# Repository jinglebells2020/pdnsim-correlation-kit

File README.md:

# pdnsim DC correlation kit, revision C — frozen predictions

This repository publishes the **frozen, blind predictions** of the pdnsim DC correlation kit
(revision C) **before any board has been measured**. pdnsim is Simulibrium's DC IR-drop
(voltage-drop) analysis for KiCad boards.

A prediction is blind only if it was published before the measurement. These files make it
possible to check, later, that the measured results were compared with predictions fixed in
advance.

**Measured accuracy: none yet.** Nothing here is a measurement. The numbers in each
`manifest.json` are pdnsim's nominal predictions for the drawn copper of each ordered board
variant, at the fab's published nominal materials.

## What is here

| Path | What it is |
|---|---|
| `kit/correlation/DC-A@JLCPCB/` | DC-A test board, as ordered from JLCPCB: KiCad board, footprints, fab files, structure list, `manifest.json` (the frozen predictions) |
| `kit/correlation/DC-A@OSHPark/` | DC-A test board, as ordered from OSH Park |
| `kit/correlation/DC-B@JLCPCB/` | DC-B 4-layer test board, as ordered from JLCPCB |
| `kit/correlation/README.md` | The kit's own description (structures, variants, the freeze procedure) |
| `SHA256SUMS` | SHA-256 of every file under `kit/` |
| `LICENSE` | Creative Commons Attribution 4.0 International |

Each variant folder holds the same set of files:

| File | What it is |
|---|---|
| `manifest.json` | The frozen predictions (schema `pdnsim-kit-manifest/2.0.0`) |
| `STRUCTURES.md` | Human-readable list of the test structures and their pads |
| `*.kicad_pcb`, `*.kicad_pro`, `fp-lib-table`, `kit.pretty/` | KiCad board, project and footprint library |
| `fab/` | Gerbers, drill files, job file and `FAB_NOTES.txt`, as sent to the fab |

Every file under `kit/` is a **byte-for-byte copy** of the same path at commit
`6089f18215fb33b6517cfd34e1e2b68f254b26f4` of the project's private development repository,
the commit that froze the three ordered variants. The kit's README refers to project files that
are not in this repository; they are not needed to check the predictions.

## Freeze record

- Frozen at: **2026-09-30T22:37:21Z** (the `frozen_at` field of each manifest).
- Freeze tag named in each manifest: `kit-revC-frozen-20260930`.
- Manifest schema: `pdnsim-kit-manifest/2.0.0`, status `frozen`.

| Variant | SHA-256 of `manifest.json` |
|---|---|
| `DC-A@JLCPCB` | `0380305942eb3074b9b0c43881a4c84dd80b9ef34d34a300505127b344b5820a` |
| `DC-A@OSHPark` | `88b3b00db004893e5cdd9a4e5d3682f16e9d32318634c68260069ee0fdbd8033` |
| `DC-B@JLCPCB` | `d98b1a52961c6c96555394d8a66fdd6cf5af46fae24080acda33ddb1f5f6e8e6` |

## Verifying the files

From the repository root:

```sh
sha256sum -c SHA256SUMS          # Linux
shasum -a 256 -c SHA256SUMS      # macOS
```

Every line must report `OK`. The same check runs in CI on every push
(`.github/workflows/verify-checksums.yml`), and `.gitattributes` stops git from rewriting line
endings, so a fresh clone matches the frozen bytes on any platform.

The boards open in KiCad 9 (board file format `20241229`). Opening a board in KiCad can
create local files (`*.kicad_prl`, backups); they are ignored by `.gitignore` and are not part
of the kit.

Not included: the fourth, provisional variant (DC-A2@JLCPCB, not ordered) and the order records
(order numbers and prices).

## Licence

The files in this repository are licensed under the Creative Commons Attribution 4.0
International licence (CC BY 4.0); see `LICENSE`.

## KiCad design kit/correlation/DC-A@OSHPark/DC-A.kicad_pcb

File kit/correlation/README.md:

# pdnsim DC correlation kit (ROADMAP M13), revision C

Manufacturable DC test boards ("coupons") for measuring how well pdnsim predicts real copper.
Every structure is a single net with on-board Kelvin (4-wire) force and sense pads, so the
quantity measured on the bench is exactly the one pdnsim computes:

    R4 = [V(S+) − V(S−)] / I

where S+ and S− are sense pads that carry no current and I is forced between F+ and F−.

> **Nothing in this folder is a measurement.** The expected values in each `manifest.json`
> are pdnsim's own nominal predictions for the drawn copper at the ordered variant's published
> nominal copper and plating, at 20 °C. No board has been fabricated or measured. pdnsim has
> **no measured accuracy** until boards are measured and the data processed; nothing in this
> kit may be quoted as one.
>
> **Status: the three ordered variants are FROZEN; DC-A2@JLCPCB is PROVISIONAL.** The
> manifests of DC-A@JLCPCB, DC-B@JLCPCB and DC-A@OSHPark were frozen at
> 2026-09-30T22:37:21Z from the committed (ordered) boards, before any board arrived or was
> measured (`freeze_tag` `kit-revC-frozen-20260930`, pdnsim commit `8ec4955508c0`, clean
> tree); DC-A2@JLCPCB was not ordered and stays provisional. The predictions use each
> structure's own via model — the corrected model (`copper.via_model: corrected`, DECISIONS
> D70–D72) for every structure, the lumped barrel for the Kelvin vias, whose quiet-side taps
> exclude the land spreading (D173). Do not compare a measurement with a provisional
> manifest.

Revision C replaces revision B (K2S/K2V/K4, 100 × 127–155 mm, never fabricated). It follows
the market research's test-board plan: three coupon designs of ≤ 100 × 100 mm, 18 boards from
two fabs (DECISIONS D150–D176 record every change and every dropped item, D400 the pre-order
re-check; the plan and its review are in `docs/kit-revC/`).

## Designs and ordered variants

A **design** is one artwork; an **ordered variant** is a design at one fab with that fab's
published nominal materials. Each variant has its own folder, board file, fab files and
manifest; the variants of one design share the artwork byte for byte (checked at build: every
Gerber except the job file, and the drill files).

| Variant (folder) | Design | Fab, quantity | Outer copper (nominal) | Plating (nominal) | Finish | Mask | Serial |
|---|---|---|---|---|---|---|---|
| `DC-A@JLCPCB/` | DC-A, 2 layers | JLCPCB, 5 | 1 oz, 35 µm | 18 µm | ENIG | green | JLCPCB `A1-0001…` |
| `DC-A@OSHPark/` | DC-A, 2 layers | OSH Park, 3 | 1 oz, 35.56 µm (1.4 mil) | 25.4 µm (1 mil) | ENIG | purple | hand-written |
| `DC-A2@JLCPCB/` | DC-A (same Gerbers) | JLCPCB, 5 | **2 oz**, 70 µm | 18 µm | ENIG | **blue** | JLCPCB `A2-0001…` |
| `DC-B@JLCPCB/` | DC-B, 4 layers | JLCPCB, 5 | 1 oz / inner 0.5 oz (15.2 µm) | 18 µm | ENIG | green | JLCPCB `B-0001…` |

Both designs are **99.06 × 99.06 mm** (39 steps of the 2.54 mm probe grid; JLCPCB's ≤ 100 ×
100 mm price tier), 1.6 mm FR-4, four 3.2 mm unplated mounting holes 4 mm from the corners.
DC-B is JLCPCB's **JLC04161H-7628** stackup (Cu 35 µm / 7628 prepreg 0.2104 mm / Cu 15.2 µm /
core 1.065 mm / Cu 15.2 µm / 7628 prepreg 0.2104 mm / Cu 35 µm, published; identical to its
default 1.6 mm 4-layer build). JLCPCB publishes no 2-layer core thickness: the DC-A core is an
**assumption** (1.51 mm at 1 oz, 1.44 mm at 2 oz) measured by micrometer on the thickness
islands and on the microsection. Every nominal carries its source (the fab page and the date
it was fetched) in the manifest's `variant.sources`; assumptions are listed in
`variant.assumptions`.

DC-A and DC-A2 are the same artwork ordered in two copper weights: they are told apart by the
**mask colour** (green / blue, an order-form option that leaves the Gerbers identical), the
JLCPCB serial prefix, and the silkscreen tick boxes `CU 1OZ □ 2OZ □  FAB JLC □ OSH □` (tick the
board's variant on arrival; a 2 oz board is also about 14 % heavier). Record the variant of
every board in the measurement file.

### What is on the boards

**DC-A** (2 layers; probed from **both faces**: front-only structures sit over back-only
ones, and back structures have their pads on B.Cu and are probed with the board flipped — the
pad grid is symmetric, so one pogo plate serves both faces):

* both faces — plane pairs with 1, 4 and 8 vias (VA1, VA4, VA8); single Kelvin vias at 0.3
  and 0.5 mm drill (KV-030, KV-050); 20-via daisy chains at both drills (DC-030W, DC-050W); a
  stacked F/B cross pair (VDP-F3/VDP-B3); via witnesses (WIT-V) and facing F/B copper
  islands for the board thickness (TK1–TK3);
* front — a 1 mm × 88 mm bar with taps 78.74 mm apart (LB-F-100, a millivolt-level check),
  the neck to 1/5 width (NK1), the 90° corner (LC), 0.5/1/2 mm bridges along x and a 0.5 mm
  bridge along y (BR-F-…), F.Cu crosses (VDP-F1, VDP-F2);
* back — a 38 × 38 mm pour with a 5 × 5 grid of keyhole sense taps fed at the midpoints of
  two edges through 4 mm feeds with 2 × 2 mm force pads (PM, the plane map; its force wires
  are **soldered**), a slotted strip (SL1-B), a 5 mm bar (BR-B-500X), a 0.5 mm bridge
  (BR-B-050X), B.Cu crosses (VDP-B1, B2, B4), and a serpentine copper RTD with a 2.8 × 5 mm
  thermocouple pad (RTD, role *thermometer*).

**DC-B** (4 layers; every pad on the front): a PDN with a BGA-like copper load on
In2 (supply) / In1 (return) planes, a 0.3 mm supply connector F → In2 and a 0.5 mm return
connector In1 → B with a B.Cu bus, and taps on all four layers (configurations P1–P7: the
pour → vias → inner plane → back path); a 26 × 16 mm In1 plane split by a 1 mm gap and joined
by a 2 mm bridge, fed through 4 mm wide, 5 mm long feeds (SP); the neck on In1 (NK1-I1); crosses on all four layers (VDP-F1, VDP-B1,
VDP-I1-1/2, VDP-I2-1/2); 0.5 and 2 mm inner bridges (BR-I1-…, BR-I2-…); the 0.25 mm strap
bridge on F.Cu (BR-F-025X); full-span Kelvin vias at both drills (KV-FB, KV-FB-050); WIT-V
and TK1–TK3.

Each variant's `STRUCTURES.md` lists every structure and configuration with pads, nominal
R4, convergence, suggested current, expected sense voltage, self-heating estimate and the
triplets the noise rule needs.

### What the research asked for and did not get (details in DECISIONS)

The 50 mm pour is 38 mm (same 5 × 5 taps; tap voltages of a scaled sheet are scale-invariant);
VA2, the 1 mm and 2 mm y-bridges, LC-I1, a DC-B RTD and a separate layer-path structure were
dropped for space (the PDN carries the layer path); the via arrays are 1, 4 and 8 vias, not 1,
4, 9 and 16 (16 barrels in parallel are about 0.1 mΩ, below the plane spreading that already
dominates VA8); the "JLCJLCJLCJLC" order-number marker is
not on the boards because **JLCPCB no longer prints order numbers** (since May 2026, and asks
customers not to add the string): the boards carry a 2 × 10 mm solid silkscreen square in the
top margin for JLCPCB's free serial number instead.

## Folder contents

| File | What |
|---|---|
| `ORDERING.md` | every order-form field per variant, the OSH Park upload, prices, what to archive |
| `ORDERED.json` | per variant: upload zip, board and artwork SHA-256 (written by `pdnsim kit --zip`); the order block is filled in by hand when ordering |
| `<variant>/<design>.kicad_pcb` | the board (KiCad 9). Zone fills are KiCad's own (refilled with KiCad's zone filler at build time), so the fab, KiCad's DRC and pdnsim see the same copper. The variants of one design differ only in the stackup section |
| `<variant>/<design>.kicad_pro` | the design rules the board was checked against |
| `<variant>/fp-lib-table`, `kit.pretty/` | the kit's footprints |
| `<variant>/fab/` | Gerbers (all copper layers, masks, silkscreens, outline), the Gerber job file (the variant's copper and finish), Excellon drill files (PTH and NPTH separate), creation-date lines removed so they are reproducible, and `FAB_NOTES.txt` (what the boards must be, for that fab) |
| `<variant>/manifest.json` | schema `pdnsim-kit-manifest/2.0.0`: the variant and its cited nominals, status (provisional / frozen), provenance (pdnsim version, git commit, clean-tree flag, via model), every structure, pad (with its layer), 4-wire configuration, nominal prediction, suggested currents with the self-heating estimate, and the design checks |
| `<variant>/STRUCTURES.md` | a readable table generated from `manifest.json` |

## Provisional → frozen (before any measurement)

A blind prediction is blind only if it was published before the measurement. The order
(on 2026-09-30, steps 1–3 were done for DC-A@JLCPCB, DC-B@JLCPCB and DC-A@OSHPark — frozen
at 2026-09-30T22:37:21Z, tag `kit-revC-frozen-20260930` created locally; publishing the tag,
step 4, is the founder's decision; DC-A2@JLCPCB is not ordered and stays at step 1):

1. **Before ordering:** the manifests are `status: provisional`. Order the boards from the
   committed fab files (`ORDERING.md`); `pdnsim kit kit/correlation --zip DIR` writes the upload zips and
   records their hashes and the board hashes in `ORDERED.json`; fill in the order block (order
   number, date, price, serial range, the stackup screenshot) and commit it.
2. **The via-model correction is merged** (DECISIONS D70–D72; the merge: D173). Every
   structure predicts with its own model (`structures[].via_model`; `nominal_model.via_model`
   is `corrected`): the Kelvin vias `lumped`, every other structure `corrected`. The manifests
   were regenerated from the committed boards (`pdnsim kit kit/correlation --from-boards`);
   the boards and fab files did not change.
3. **Freeze** on a clean checkout: `pdnsim kit kit/correlation --freeze`. It refuses (exit 2)
   while the via-model correction is missing, while the source tree has uncommitted changes, or
   when a board differs from the one recorded in `ORDERED.json`; otherwise it re-predicts from
   the committed boards (the boards and fab files are not touched and must still be the
   generator's output) and writes `status: frozen`, `frozen_at` (UTC) and `freeze_tag`.
4. **Publish before the first reading:** commit, create the tag named in `freeze_tag`, push it
   to the public remote (a third party then attests its time) and record the tag and the
   release URL in the measurement file (`kits[].release`). `pdnsim correlate` refuses a
   provisional manifest unless `--allow-provisional` and states in every measured result
   whether it is blind (docs/CORRELATION.md §8).

## Ordering (summary; every field is in `ORDERING.md`)

* **JLCPCB** (DC-A, DC-A2, DC-B; one combined shipment): upload `DC-A_JLCPCB_revC.zip`,
  `DC-A2_JLCPCB_revC.zip`, `DC-B_JLCPCB_revC.zip` (the variant id with `_` for `@`: JLCPCB's
  uploader refuses `@` in a file name; D400); FR-4,
  1.6 mm, **ENIG** (a surcharge; **not OSP**, which JLCPCB's form excludes from physical contact
  areas — every pad here is spring-probed; **never HASL** — solder in an open via barrel
  changes its resistance by tens of per cent), vias **tented** (DC-A, DC-A2) or **plugged**
  (DC-B: JLCPCB's 4-layer form has no Tented; a via JLCPCB cannot ink-plug is to be tented;
  never open, never epoxy- or copper-filled), outer
  copper 1 oz (DC-A, DC-B) or **2 oz** (DC-A2), DC-B stackup **JLC04161H-7628** with inner
  copper 0.5 oz, mask green (DC-A, DC-B) or **blue** (DC-A2), Mark on PCB → serial number only
  at the specified position (prefixes `A1-`, `A2-`, `B-`), *Confirm Production File*, and the
  PCB Remark from `ORDERING.md` (JLCPCB reads no text inside the zip; each variant's is also in
  its `FAB_NOTES.txt`; DC-B has its own: plugged vias, the drills to plug, no fill).
* **OSH Park** (DC-A, 3 boards): upload `DC-A_OSHPark_revC.zip` (or the board file
  `DC-A_OSHPark.kicad_pcb`), 2 Layer
  Prototype service (1 oz, ENIG, purple); $5 per square inch per set of three, free shipping.
* Order all three JLCPCB designs **and** the OSH Park set: the fab-to-fab and 1 oz / 2 oz
  comparisons need them all. Keep one board of each variant for a microsection after its
  readings.

## Design rules (rev C)

One rule set valid for JLCPCB 2-layer 1 oz and 2 oz, JLCPCB 4-layer and OSH Park 2-layer, with
margin; the sources are quoted in `pdnsim.kit.rules.RULE_SOURCES` (pages fetched 2026-09-27)
and every value is in each manifest's `rules`:

* track ≥ 0.25 mm (the sense spokes, RTD lines and the 0.25 mm bridge are at it; JLCPCB 2 oz
  minimum 0.16 mm with ±20 % width tolerance; OSH Park 6 mil); clearance ≥ 0.25 mm; **same-net
  gaps ≥ 0.25 mm** (JLCPCB's same-net spacing; checked by the kit's topology check, which KiCad
  cannot do);
* vias follow JLCPCB's via rule (diameter ≥ hole + 0.1 mm, 0.15 mm preferred; "vias are treated
  differently from pads"): DC-A 0.30/0.75 and 0.50/1.00 mm, DC-B 0.30/0.70 and 0.50/0.90 mm;
  every trace-fed land/drill ≤ 2.5 (the via-model correction's validated domain, checked at
  build); **every plated hole is a via**, witnesses included, so the drill files have one
  plated tool per drill; the drill file's sizes are **finished** holes (the fabs' convention),
  while pdnsim's barrel (either via model) reads them as the drilled diameter — each
  manifest's variant assumptions give the resulting bias of prediction (a) per drill (D172);
  no surcharge on JLCPCB's form for a via hole ≥ 0.3 mm and a diameter ≥ 0.4 mm;
* hole-to-hole ≥ 0.45 mm, hole to other copper ≥ 0.30 mm, copper to edge ≥ 0.5 mm, structures
  ≥ 3 mm from the edge, no copper within 1 mm of a mounting hole, no mask opening within 4 mm
  of a mounting-hole centre (washer);
* solder mask 1:1 on the pads; every via land ≥ 0.20 mm from any mask opening (JLCPCB's 2 oz
  mask bridge; checked at build); every via covered by mask in the Gerbers (tented; JLCPCB
  plugs DC-B's 4-layer vias, D400);
* silkscreen text ≥ 1.0 mm high with a ≥ 0.16 mm stroke, ≥ 0.15 mm from every pad (JLCPCB's
  pad-to-silkscreen rule, in the DRC rules); a silkscreen ID next to every structure and a role
  label next to every pad;
* no thermal reliefs anywhere in a structure (zones connect pads solid); a netless balancing
  pour at a 0.5 mm gap on every layer.

`kicad-cli pcb drc` with the board's own project rules reports **0 violations and 0
unconnected items** on every variant (recorded in each `manifest.json`).

## How the structures are built

* **Probe pads** are single SMD pads (1.6 mm sense pads; force pads as wide as the conductor,
  except the plane map's 2 × 2 mm pads), every pad centre on the **2.54 mm grid** from the
  board's top-left corner (front view). Back pads are on B.Cu; the board width is a whole
  number of grid steps, so they are on the grid of the flipped board too. Inner and
  opposite-layer structures are reached through vias: force vias outside the sense span,
  zero-current sense vias for sense.
* **Force feeds** reach from a force pad (or force-via row) to the nearest tap over ≥ 2 × the
  conductor width. The manifest's **injection check** solves each structure with a 0.25 mm
  probe tip anywhere on each force pad and with ±10 % scatter between the barrels of each
  force-via group: every reading must change by ≤ 0.02 %.
* **Sense taps** are dead-end 0.25 mm spokes from the conductor edge, or keyholes (an island
  joined by one spoke) where a sense point sits inside a plane; the plane map's spokes run
  across the current, so a tap reads its hole centre whatever the hole's etch.
* **No pad lies in a current path**: the DC-B BGA load is copper only (balls, dogbones and
  straps are drawn as copper, not pads). The manifest's **topology check** proves on the
  finished board that each net has exactly its intended copper pieces, via lands and pads,
  that every pad is a dead end, and that same-net gaps are ≥ 0.25 mm — between pieces and
  inside one piece (a slot or a pinch; D176).
* **van der Pauw crosses** (1 mm arms) on every measured layer, spread over the board; the
  manifest records pdnsim's finite-contact error of each drawn cross (must be ≤ 0.1 %) and
  `STRUCTURES.md` lists the two crosses nearest each validation structure.
* **Witnesses:** WIT-V holds two vias of each drill, in the same Excellon tool as the measured
  vias, for the microsection (barrel wall, finished hole, land registration); TK1–TK3 are
  facing 3 × 3 mm bare-copper islands on F.Cu and B.Cu for a micrometer reading of the board
  thickness (the barrel length of every via prediction).

## Currents and self-heating

Each structure's `current` gives I_max and the three levels I_max, I_max/√2, I_max/2 (the
zero-power fit removes steady heating). I_max is the largest current within the structure's
cap (1 A; the plane map 3 A; the RTD 20 mA) whose **heuristic** self-heating estimate of the
sensed copper stays within 0.5 °C (RTD 0.02 °C): a whole-board thin-fin model (FR-4 plus the
board's copper, still air at 20 W/m²K from both faces, no credit for probes, leads or a
backing plate) fed by pdnsim's own loss map at 1 A plus the force contacts, **plus a local
line-source term** for every element: the rise of a conductor above the copper around it
through the FR-4 (the pour across its gap, the nearest copper above and below), which the fin
alone misses and which dominates on the narrow bridges and bars (review MET-1, D171). The
estimate is conservative in named respects (no conduction along a conductor to its wide ends,
no credit for the fixture) but it is not a bound. The plan assumes spring probes of **≤ 20 mΩ**
per force contact (the plane map: soldered leads); the manifest gives the extra rise per 10 mΩ
of contact (`delta_t_per_10mohm_contact_c`) and the current allowed with soldered force leads
(`i_max_soldered_a`). Record the two-wire force-path resistance of every reading
(`two_wire_ohm`): `pdnsim correlate` estimates the contacts from it and reports the extra
heating they imply (`FORCE_CONTACT`, a warning above the limit). `triplets_per_level` is the
number of current-reversal triplets per level for a zero-power reading with the structure's
`noise_target_rel` (0.1 %; the crosses 0.3 %, their spatial copper spread being several %) at
0.3 µV reading noise; `STRUCTURES.md` and the manifest's `summary` give the bench time.

## Measuring (summary; the protocol is [docs/CORRELATION.md](../../docs/CORRELATION.md))

* Support the board on a full-area insulating plate with reliefs for the other face's pads,
  joints and the thermocouple; probe the front first, then solder the plane-map force wires
  and probe the back.
* Current reversal (+I, −I, +I) at each level, levels in ascending order or after the board
  has returned to equilibrium; log the temperature (the RTD tracks drift to ~0.02 K once
  calibrated against the thermocouple pad).
* van der Pauw: all four configurations of each cross; the general vdP equation.
* Micrometer every board's thickness on TK1–TK3 with a contact ≤ 2.5 mm centred on each island
  (a flat anvil sits on the mask around it; docs/CORRELATION.md §3, D400); after the readings,
  section one board per variant through WIT-V (and chain barrels): wall thickness and finished
  hole per drill.
* Record the readings in a measurement file (`pdnsim correlate --template
  kit/correlation/DC-A@JLCPCB/manifest.json --serial A1-0001 --output meas.yaml`) and run
  `pdnsim correlate meas.yaml --out DIR`. `pdnsim correlate --self-test` checks that pipeline
  on synthetic data — it is not a measurement.

## Regenerating

```bash
pdnsim kit --list                                  # designs, variants, status
pdnsim kit kit/correlation                         # every variant; needs KiCad 9 (pcbnew + kicad-cli)
pdnsim kit kit/correlation -c DC-A --copper 2oz    # one variant (DC-A2@JLCPCB)
pdnsim kit kit/correlation --zip OUT               # + upload zips (no '@'), OSH Park board, SHA256SUMS
pdnsim kit kit/correlation --from-boards           # re-predict from the committed boards
pdnsim kit /tmp/k --no-kicad --no-predictions      # quick pdnsim-only build (no fab files)
```

The build is deterministic: the same pdnsim and KiCad versions give byte-identical boards, fab
files and zips (the manifests also record the pdnsim commit they were built from).
`tests/unit/test_correlation_boards.py` checks the committed files against the generator and
re-computes predictions; `tests/unit/test_kit_variants.py` the variants, freeze rules and
zips; `tests/e2e/test_correlation_boards_kicad.py` (KiCad) re-runs the refill, DRC and fab
export.

## Known limitations

* The DC-A core thickness and the finished copper of every variant are nominal values until
  measured (micrometer, vdP crosses, microsection); JLCPCB publishes no finished 2 oz thickness
  and the DC-A2 plating is assumed equal to the 1 oz plating (use DC-A2's own microsection).
* The predictions are PROVISIONAL until frozen. The via structures use the corrected via model
  (the Kelvin vias the lumped barrel), which agrees with a 3-D reference, not with a
  measurement; each structure's `notes` list what the via model leaves out (D71).
* Etch bias is measured by the bridges (F.Cu along x and y, B.Cu along x on DC-A, F.Cu and
  the inner layers along x on DC-B) and applied by `pdnsim correlate` to prediction (b) to
  first order; a direction without a bridge borrows the other with a bound, DC-B's B.Cu is only
  bounded.
* The 0.5 mm vias are at JLCPCB's tenting limit; a leaky tent on OSH Park's ENIG boards may
  put nickel into a barrel (inspect every tent over a measured via; the microsection shows it).
* ENIG covers every mask-free pad: the micrometer reading over TK1–TK3 (contact ≤ 2.5 mm on
  the island) includes the finish of both faces (+6–12 µm, ≤ 0.8 % of the span; not
  subtracted); a flat anvil would add the mask and silkscreen around the islands (+10–80 µm)
  and is not a valid reading.
* Prediction (a) reads each drawn via drill as the drilled diameter; if the fab finishes the
  hole as drawn, the real barrels have 7–16 % less resistance than (a) (per drill and variant
  in the manifest's assumptions); (b) uses the microsection and is immune.
* The self-heating estimate is a heuristic (conservative in named respects, not a bound), not
  a thermal prediction; the three-level fit measures the real heating.

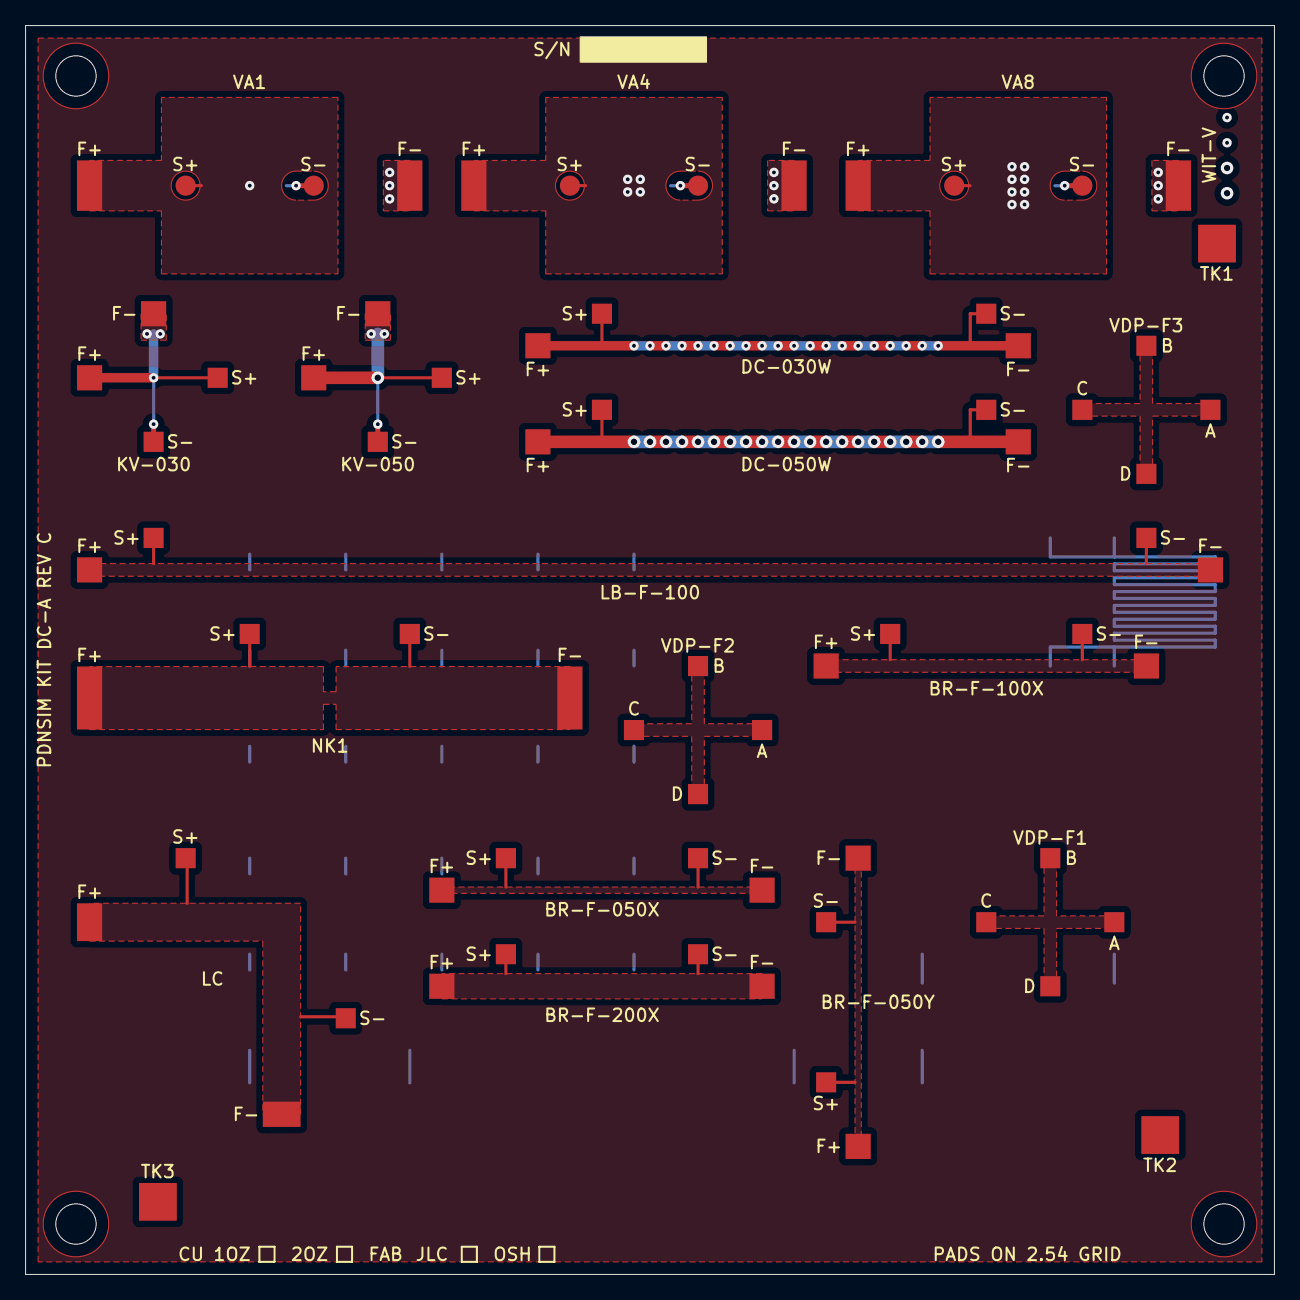
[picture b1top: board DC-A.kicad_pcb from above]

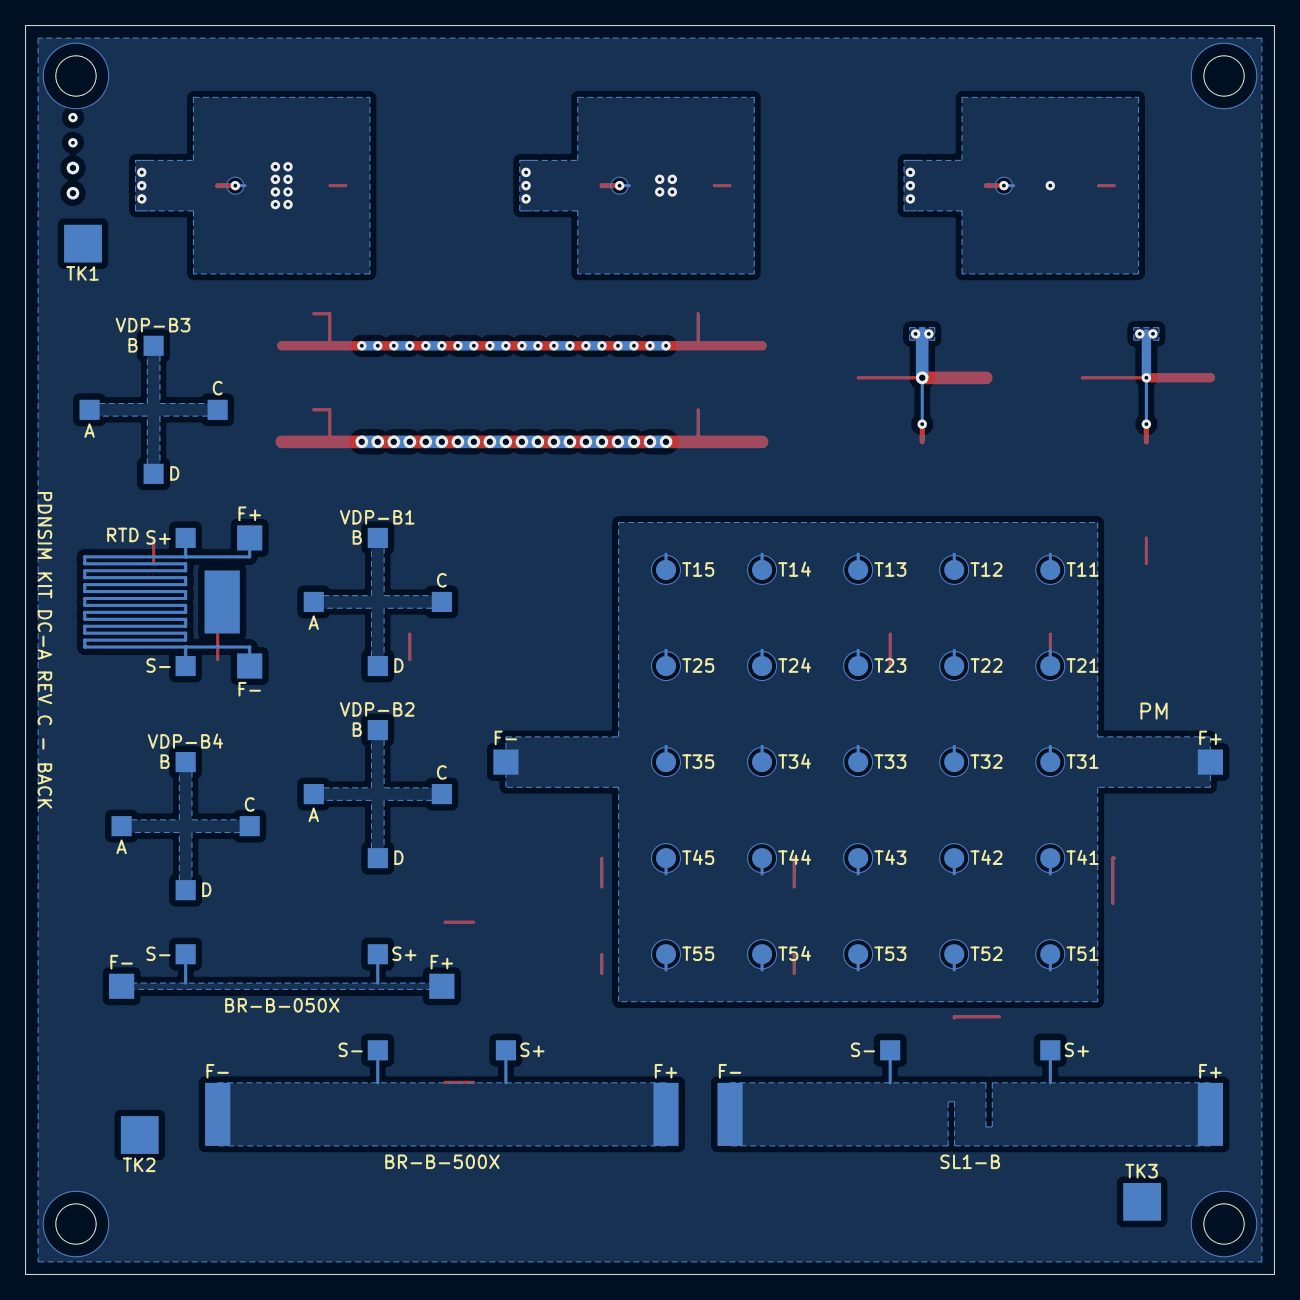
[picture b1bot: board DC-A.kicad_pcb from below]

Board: 2 copper layers, 99.1 x 99.1 mm, 138 parts (63 on the bottom side), 26 nets.

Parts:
BRB050X_FM, BRB050X_FP: ForcePad_2.0x2.0mm
BRB050X_SM, BRB050X_SP, BRB500X_SM, BRB500X_SP: ProbePad_1.6x1.6mm
BRB500X_FM, BRB500X_FP: ForcePad_2.0x5.0mm
BRF050X_FM, BRF050X_FP, BRF050Y_FM, BRF050Y_FP, BRF100X_FM, BRF100X_FP, BRF200X_FM, BRF200X_FP: ForcePad_2.0x2.0mm
BRF050X_SM, BRF050X_SP, BRF050Y_SM, BRF050Y_SP, BRF100X_SM, BRF100X_SP, BRF200X_SM, BRF200X_SP: ProbePad_1.6x1.6mm
DC030W_FM, DC030W_FP, DC050W_FM, DC050W_FP: ForcePad_2.0x2.0mm
DC030W_SM, DC030W_SP, DC050W_SM, DC050W_SP: ProbePad_1.6x1.6mm
H1, H2, H3, H4: MountingHole_3.2mm
KV030_FM, KV030_FP, KV050_FM, KV050_FP: ForcePad_2.0x2.0mm
KV030_SM, KV030_SP, KV050_SM, KV050_SP: ProbePad_1.6x1.6mm
LBF100_FM, LBF100_FP: ForcePad_2.0x2.0mm
LBF100_SM, LBF100_SP: ProbePad_1.6x1.6mm
LC_FM: ForcePad_3.0x2.0mm
LC_FP: ForcePad_2.0x3.0mm
LC_SM: ProbePad_1.6x1.6mm
LC_SP: ProbePad_1.6x1.6mm
NK1_FM, NK1_FP: ForcePad_2.0x5.0mm
NK1_SM, NK1_SP: ProbePad_1.6x1.6mm
PM_FM: ForcePad_2.0x2.0mm
PM_FP: ForcePad_2.0x2.0mm
PM_T11, PM_T12, PM_T13, PM_T14, PM_T15, PM_T21, PM_T22, PM_T23, PM_T24, PM_T25, PM_T31, PM_T32, PM_T33, PM_T34, PM_T35, PM_T41, PM_T42, PM_T43, PM_T44, PM_T45, PM_T51, PM_T52, PM_T53, PM_T54, PM_T55: ProbePad_D1.6mm
RTD_FM: ForcePad_2.0x2.0mm
RTD_FP: ForcePad_2.0x2.0mm
RTD_SM: ProbePad_1.6x1.6mm
RTD_SP: ProbePad_1.6x1.6mm
RTD_W1: ThermocouplePad_2.8x5.0mm
SL1B_FM, SL1B_FP: ForcePad_2.0x5.0mm
SL1B_SM, SL1B_SP: ProbePad_1.6x1.6mm
TK1_W1, TK1_W2, TK2_W1, TK2_W2, TK3_W1, TK3_W2: ThicknessIsland_3.0x3.0mm
VA1_FM, VA1_FP, VA4_FM, VA4_FP, VA8_FM, VA8_FP: ForcePad_2.0x4.0mm
VA1_SM, VA1_SP, VA4_SM, VA4_SP, VA8_SM, VA8_SP: ProbePad_D1.6mm
VDPB1_A, VDPB1_B, VDPB1_C, VDPB1_D, VDPB2_A, VDPB2_B, VDPB2_C, VDPB2_D, VDPB3_A, VDPB3_B, VDPB3_C, VDPB3_D, VDPB4_A, VDPB4_B, VDPB4_C, VDPB4_D: ProbePad_1.6x1.6mm
VDPF1_A, VDPF1_B, VDPF1_C, VDPF1_D, VDPF2_A, VDPF2_B, VDPF2_C, VDPF2_D, VDPF3_A, VDPF3_B, VDPF3_C, VDPF3_D: ProbePad_1.6x1.6mm

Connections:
BR-B-050X: BRB050X_FM.1, BRB050X_FP.1, BRB050X_SM.1, BRB050X_SP.1
BR-B-500X: BRB500X_FM.1, BRB500X_FP.1, BRB500X_SM.1, BRB500X_SP.1
BR-F-050X: BRF050X_FM.1, BRF050X_FP.1, BRF050X_SM.1, BRF050X_SP.1
BR-F-050Y: BRF050Y_FM.1, BRF050Y_FP.1, BRF050Y_SM.1, BRF050Y_SP.1
BR-F-100X: BRF100X_FM.1, BRF100X_FP.1, BRF100X_SM.1, BRF100X_SP.1
BR-F-200X: BRF200X_FM.1, BRF200X_FP.1, BRF200X_SM.1, BRF200X_SP.1
DC-030W: DC030W_FM.1, DC030W_FP.1, DC030W_SM.1, DC030W_SP.1
DC-050W: DC050W_FM.1, DC050W_FP.1, DC050W_SM.1, DC050W_SP.1
KV-030: KV030_FM.1, KV030_FP.1, KV030_SM.1, KV030_SP.1
KV-050: KV050_FM.1, KV050_FP.1, KV050_SM.1, KV050_SP.1
LB-F-100: LBF100_FM.1, LBF100_FP.1, LBF100_SM.1, LBF100_SP.1
LC: LC_FM.1, LC_FP.1, LC_SM.1, LC_SP.1
NK1: NK1_FM.1, NK1_FP.1, NK1_SM.1, NK1_SP.1
PM: PM_FM.1, PM_FP.1, PM_T11.1, PM_T12.1, PM_T13.1, PM_T14.1, PM_T15.1, PM_T21.1, PM_T22.1, PM_T23.1, PM_T24.1, PM_T25.1, PM_T31.1, PM_T32.1, PM_T33.1, PM_T34.1, PM_T35.1, PM_T41.1, PM_T42.1, PM_T43.1, PM_T44.1, PM_T45.1, PM_T51.1, PM_T52.1, PM_T53.1, PM_T54.1, PM_T55.1
RTD: RTD_FM.1, RTD_FP.1, RTD_SM.1, RTD_SP.1
SL1-B: SL1B_FM.1, SL1B_FP.1, SL1B_SM.1, SL1B_SP.1
VA1: VA1_FM.1, VA1_FP.1, VA1_SM.1, VA1_SP.1
VA4: VA4_FM.1, VA4_FP.1, VA4_SM.1, VA4_SP.1
VA8: VA8_FM.1, VA8_FP.1, VA8_SM.1, VA8_SP.1
VDP-B1: VDPB1_A.1, VDPB1_B.1, VDPB1_C.1, VDPB1_D.1
VDP-B2: VDPB2_A.1, VDPB2_B.1, VDPB2_C.1, VDPB2_D.1
VDP-B3: VDPB3_A.1, VDPB3_B.1, VDPB3_C.1, VDPB3_D.1
VDP-B4: VDPB4_A.1, VDPB4_B.1, VDPB4_C.1, VDPB4_D.1
VDP-F1: VDPF1_A.1, VDPF1_B.1, VDPF1_C.1, VDPF1_D.1
VDP-F2: VDPF2_A.1, VDPF2_B.1, VDPF2_C.1, VDPF2_D.1
VDP-F3: VDPF3_A.1, VDPF3_B.1, VDPF3_C.1, VDPF3_D.1

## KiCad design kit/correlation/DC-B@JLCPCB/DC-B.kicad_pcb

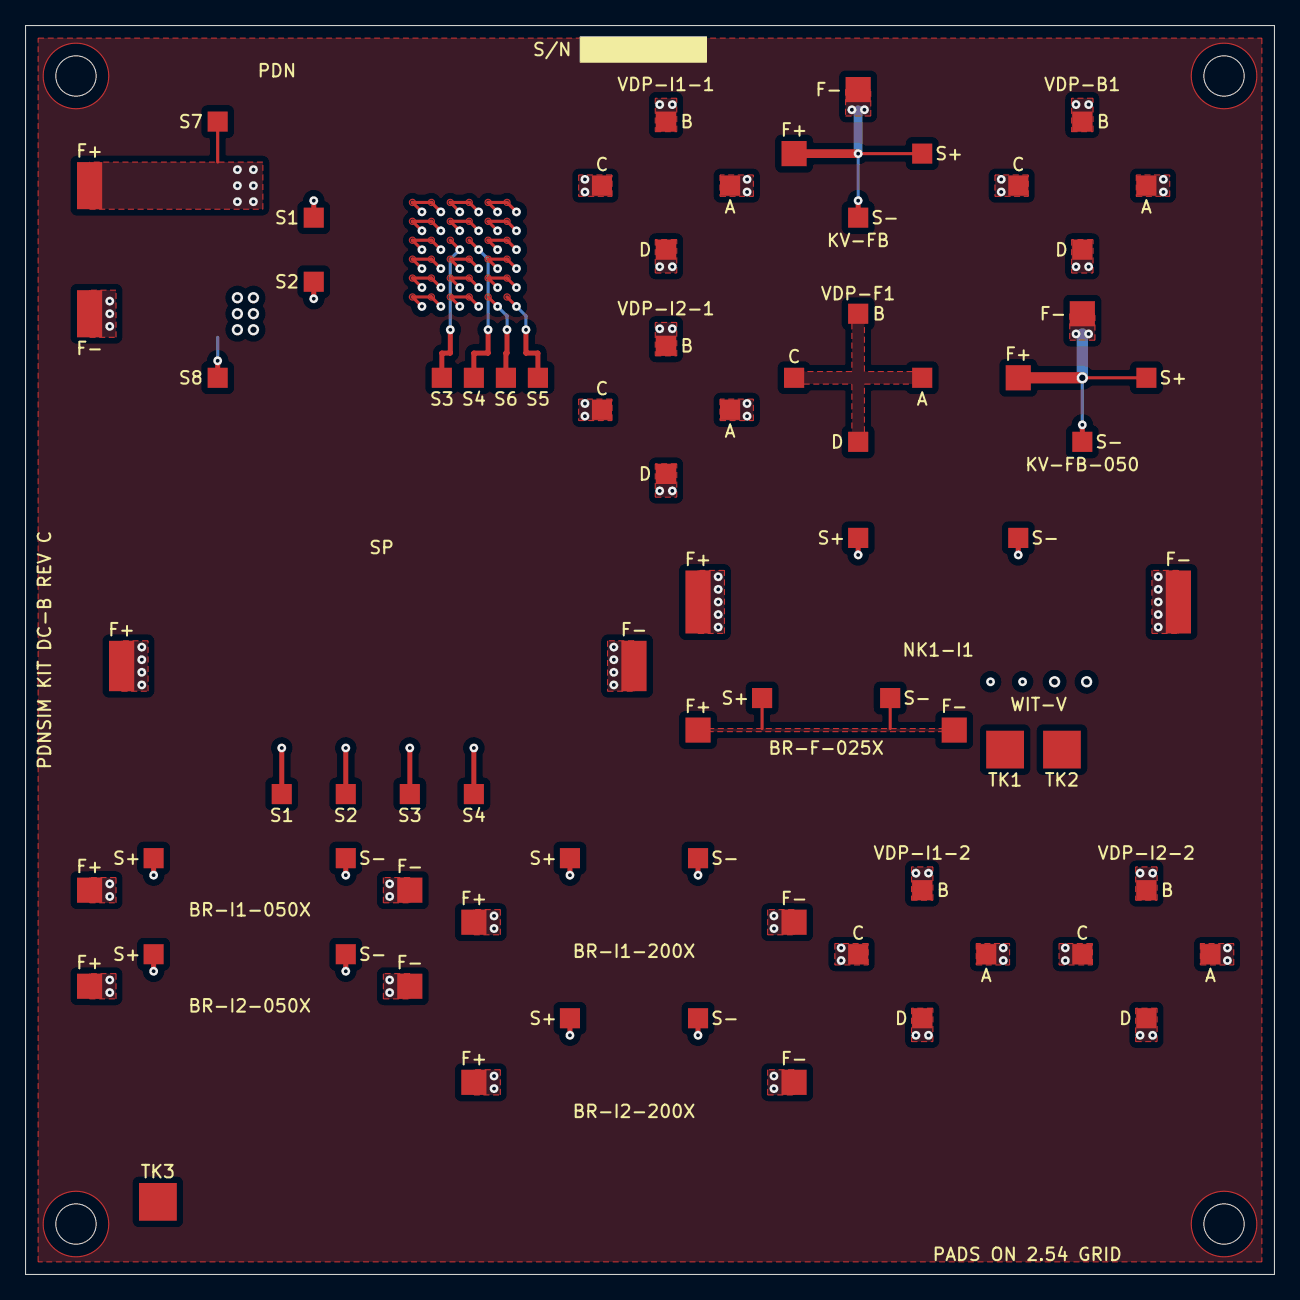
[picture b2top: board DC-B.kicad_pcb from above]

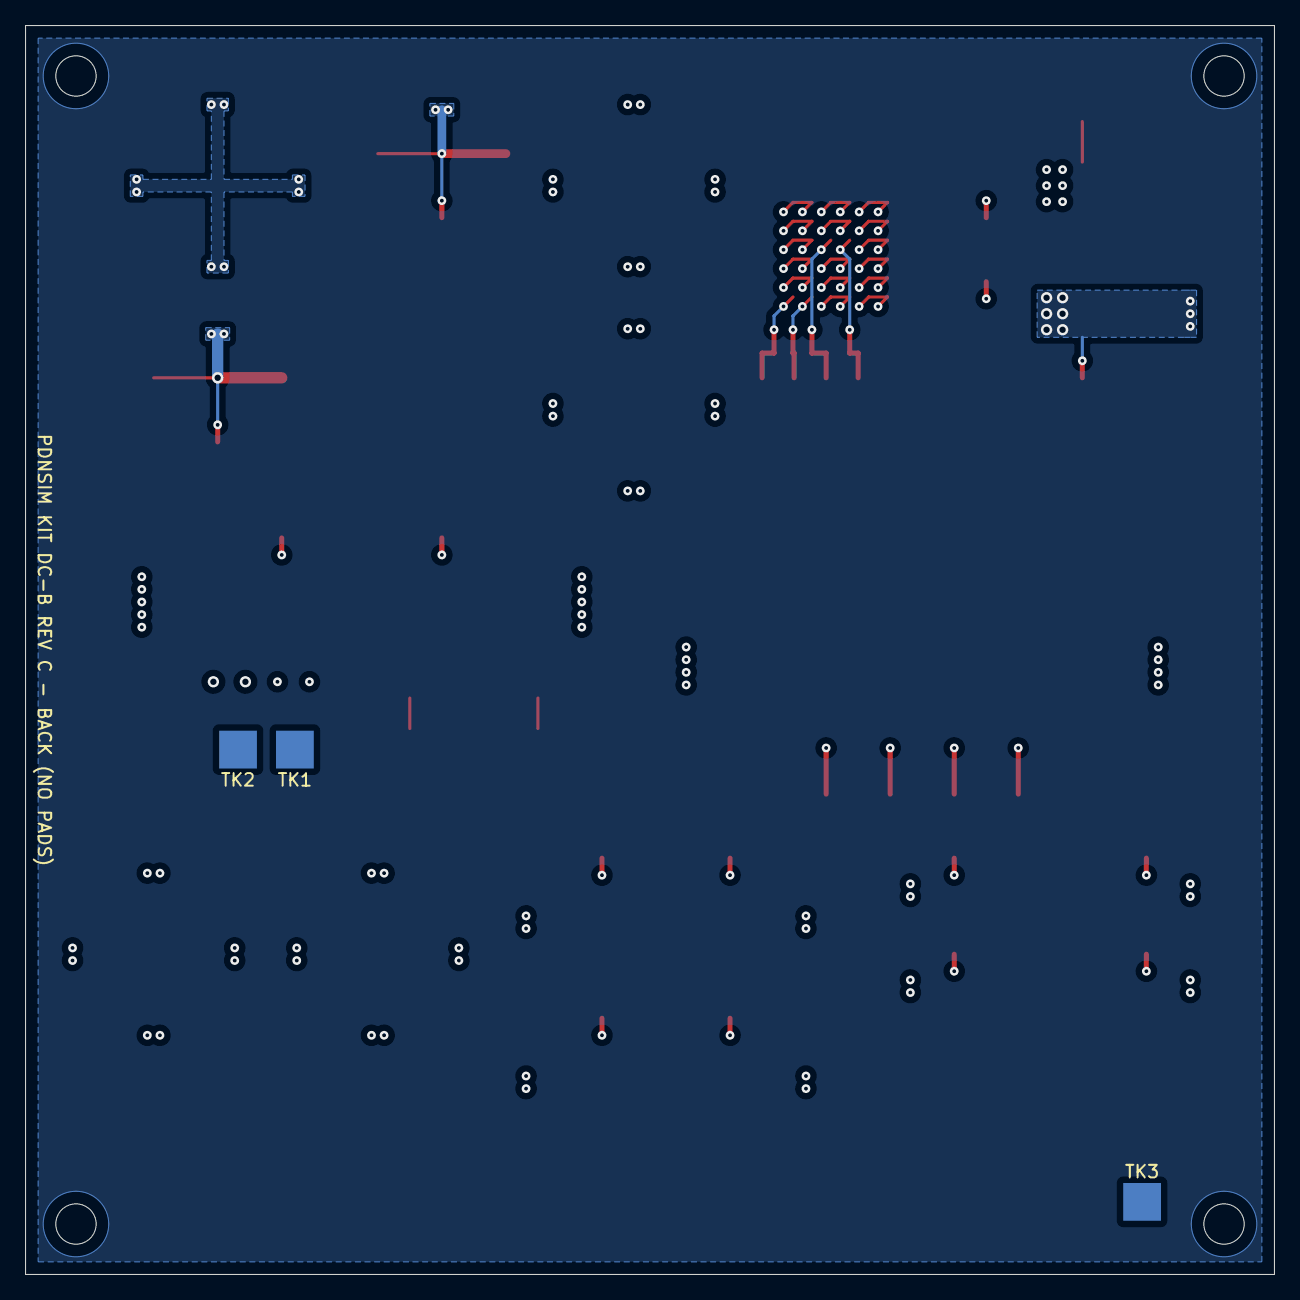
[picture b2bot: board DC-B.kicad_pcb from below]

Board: 4 copper layers, 99.1 x 99.1 mm, 82 parts (3 on the bottom side), 16 nets.

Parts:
BRF025X_FM, BRF025X_FP: ForcePad_2.0x2.0mm
BRF025X_SM, BRF025X_SP: ProbePad_1.6x1.6mm
BRI1050X_FM, BRI1050X_FP, BRI1200X_FM, BRI1200X_FP, BRI2050X_FM, BRI2050X_FP, BRI2200X_FM, BRI2200X_FP: ForcePad_2.0x2.0mm
BRI1050X_SM, BRI1050X_SP, BRI1200X_SM, BRI1200X_SP, BRI2050X_SM, BRI2050X_SP, BRI2200X_SM, BRI2200X_SP: ProbePad_1.6x1.6mm
H1, H2, H3, H4: MountingHole_3.2mm
KVFB050_FM, KVFB050_FP: ForcePad_2.0x2.0mm
KVFB050_SM, KVFB050_SP: ProbePad_1.6x1.6mm
KVFB_FM: ForcePad_2.0x2.0mm
KVFB_FP: ForcePad_2.0x2.0mm
KVFB_SM: ProbePad_1.6x1.6mm
KVFB_SP: ProbePad_1.6x1.6mm
NK1I1_FM, NK1I1_FP: ForcePad_2.0x5.0mm
NK1I1_SM, NK1I1_SP: ProbePad_1.6x1.6mm
PDN_FM: ForcePad_2.0x3.74mm
PDN_FP: ForcePad_2.0x3.74mm
PDN_S1, PDN_S2, PDN_S3, PDN_S4, PDN_S5, PDN_S6, PDN_S7, PDN_S8: ProbePad_1.6x1.6mm
SP_FM: ForcePad_2.0x4.0mm
SP_FP: ForcePad_2.0x4.0mm
SP_S1, SP_S2, SP_S3, SP_S4: ProbePad_1.6x1.6mm
TK1_W1, TK1_W2, TK2_W1, TK2_W2, TK3_W1, TK3_W2: ThicknessIsland_3.0x3.0mm
VDPB1_A, VDPB1_B, VDPB1_C, VDPB1_D: ProbePad_1.6x1.6mm
VDPF1_A, VDPF1_B, VDPF1_C, VDPF1_D: ProbePad_1.6x1.6mm
VDPI11_A, VDPI11_B, VDPI11_C, VDPI11_D, VDPI12_A, VDPI12_B, VDPI12_C, VDPI12_D, VDPI21_A, VDPI21_B, VDPI21_C, VDPI21_D, VDPI22_A, VDPI22_B, VDPI22_C, VDPI22_D: ProbePad_1.6x1.6mm

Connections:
BR-F-025X: BRF025X_FM.1, BRF025X_FP.1, BRF025X_SM.1, BRF025X_SP.1
BR-I1-050X: BRI1050X_FM.1, BRI1050X_FP.1, BRI1050X_SM.1, BRI1050X_SP.1
BR-I1-200X: BRI1200X_FM.1, BRI1200X_FP.1, BRI1200X_SM.1, BRI1200X_SP.1
BR-I2-050X: BRI2050X_FM.1, BRI2050X_FP.1, BRI2050X_SM.1, BRI2050X_SP.1
BR-I2-200X: BRI2200X_FM.1, BRI2200X_FP.1, BRI2200X_SM.1, BRI2200X_SP.1
KV-FB: KVFB_FM.1, KVFB_FP.1, KVFB_SM.1, KVFB_SP.1
KV-FB-050: KVFB050_FM.1, KVFB050_FP.1, KVFB050_SM.1, KVFB050_SP.1
NK1-I1: NK1I1_FM.1, NK1I1_FP.1, NK1I1_SM.1, NK1I1_SP.1
PDN: PDN_FM.1, PDN_FP.1, PDN_S1.1, PDN_S2.1, PDN_S3.1, PDN_S4.1, PDN_S5.1, PDN_S6.1, PDN_S7.1, PDN_S8.1
SP: SP_FM.1, SP_FP.1, SP_S1.1, SP_S2.1, SP_S3.1, SP_S4.1
VDP-B1: VDPB1_A.1, VDPB1_B.1, VDPB1_C.1, VDPB1_D.1
VDP-F1: VDPF1_A.1, VDPF1_B.1, VDPF1_C.1, VDPF1_D.1
VDP-I1-1: VDPI11_A.1, VDPI11_B.1, VDPI11_C.1, VDPI11_D.1
VDP-I1-2: VDPI12_A.1, VDPI12_B.1, VDPI12_C.1, VDPI12_D.1
VDP-I2-1: VDPI21_A.1, VDPI21_B.1, VDPI21_C.1, VDPI21_D.1
VDP-I2-2: VDPI22_A.1, VDPI22_B.1, VDPI22_C.1, VDPI22_D.1
